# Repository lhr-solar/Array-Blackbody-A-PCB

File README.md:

# RTD and Irradiance Sensor Board

This repository contains the following files for the RTD/Irradiance Sensor HW:

- Schematic
- Layout
- Datasheets

Also a good resource is the
[Irradiance/RTD Board Parts List](https://docs.google.com/spreadsheets/d/1edYMT-QyYtll1uI2qYTIh2mhwAQPUqRFkjrvS2jViS4/edit?usp=sharing);
this is the source of truth for the schematic and layout and should be consulted
and updated by anyone doing revisions on the board. As good practice, make sure
your updates to the parts list, when finalized, gets a new named version in the
version history.

A couple other important sections for engineers who are improving this board are
below.

- Versioning
- Maintainers
- Errata and Changes
- Suggested Improvements
- Ordering Instructions
- Assembly Instructions

---

## Maintainers

The last maintainer of this project was Matthew Yu (Array Lead 2020) as of
12/13/2020. His email is matthewjkyu@gmail.com.

Also a useful point of contact is Professor Gary Hallock, who advised Matthew
and worked with the several former senior design teams and solar car class
groups who developed this board.

---

## Versioning, Errata, and Changes

This board has separate versions for the schematic, parts list, and layout. We
use [semantic versioning](https://semver.org/) to denote between versions.

We also follow the mutually inclusive versioning procedure agreed upon in this
[issue](https://github.com/lhr-solar/Electronics/issues/40).

### Versioning

The board schematic is currently on **Version 1.0.0**.

The board layout is currently on **Version 1.0.0**.

The parts list is currently on **Version 1.0.0**.

### Schematic

- **Rev 1.0.0**:
  - None as of 12/13/2020, but then the board hasn't been assembled and tested
    yet.

### Layout

- **Rev 1.0.0**:
  - None as of 12/13/2020, but then the board hasn't been assembled and tested
    yet.

### Parts List

- **Rev 1.0.0**:
  - Populated and ready for ordering (sans snubber caps and resistors).

---

## Suggested Improvements

This is a list of changes we can make to the board in future versions to improve
it in various ways. Some of these are functional, others are purely aesthetic.

1. Use a multiplexer to route RTDs to a single RTD-to-digital-converter chip.
   This would reduce our 8 chips into 1 and potentially cut down board size by
   more than 50%. This may also have advantages for digital signal integrity by
   drastically reducing trace length. Oh, and a large cost reduction.
2. Rename the project from RTDTemp to RTD_Irradiance_Board. Make sure you do
   this on a feature branch of the repo so you can revert to a previous version
   if you break things.

---

## Ordering Instructions

Ordering the board will vary from distributor to distributor; some will take the
KiCAD project directly, others require Gerber files. If they require gerber
files, some will require specific naming conventions for each layer.

If they take KiCAD projects directly, that should be what you prefer. Package
`RTDTemp.pro`, `RTDTemp.kicad_pcb`, and `RTDTemp.sch` together into a zip file (i.e.
`RTDTemp.zip`) and upload it. Double check the layers they detect to ensure that
everything looks correct. If they aren't interpreted correctly, use the Gerber
files instead.

The Gerber files are grouped together into the 'Gerber/' folder. The layers you
want are:

- Front/Top Copper,
- Back/Bottom Copper,
- Front/Top Mask,
- Back/Bottom Mask,
- Front/Top Silkscreen,
- Back/Bottom Silkscreen,
- Edge Cuts (i.e. board outline)

You may also want the Front/Top Fabrication layer if you're submitting to a
manufacturer that will place and solder your components for you, but that's not
strictly necessary.

The Gerber files I've generated should be named appropriately for most
manufacturers, however they may prefer slightly different conventions. Double
check their requirements, make any necessary adjustments to file names, then zip
up all of the gerber files and upload that.

Some examples of alternate conventions:

- Some want the board outline to have the extension '.gko'.
- Some want all layers to have the same base name (i.e. 'RTDTemp.gbl',
  'RTDTemp.gbs', etc.).
- Some want the drill files combined (in which case you'll need to regenerate
  the drill file with plated and nonplated holes combined).
- Some want the drill files to have the extension '.txt'.

If you need to regenerate the Gerber files for whatever reason, the defaults
saved to the PCB file should be sufficient. However, in case these are lost,
here are the important parts:

- Set Output Directory to "Gerber/"
- Uncheck "Plot sheet reference on all layers"
- Check "Exclude PCB edge layer from other layers"
- Check "Use Protel filename extensions"

-or the drill files:

- Set Output Directory to "Gerber/"
- Set Drill Units to "Inches"
- Set Zeros Format to "Decimal format"
- Set Drill Map File Format to "PostScript"
- Uncheck "Mirror y axis"

These settings should work, but double check with your manufacturer that these
settings are correct before you order.

---

## Assembly and Testing

The board should be assembled and tested in sections to ensure proper
functioning. Assembly should go through the following sections in order:

1. Power Regulation
2. LEDs
3. Nucleo Connections
4. RTD Sensors
5. Irradiance Sensors
6. CAN

### Step by Step Instructions

It's highly recommended to pull up the schematic and layout side by side while
assembling and testing the board. As a tip, you can click on the schematic
symbol, and if the layout window is open, it'll jump to that part on the layout.
Also hide everything except the Silkscreen or Fabrication layer (of the right
side of the PCB) to remove any clutter from the layout.

Also, if you find any discrepancies between these instructions and the board
layout, please file a PR or issue so it can be fixed!

1. Initial Board Checks

   Before installing anything, check for power shorts where there shouldn't be:
   - Between Car Power +12V and GNDPWR.
   - Between Device Power +9VA and GNDREF.
   - Between Car Power +12V and Device Power +9VA.
   - Between Car Power GNDPWR and Device Power GNDREF.
   - Between CAN Iso Vout and GndOut
   - Between CAN Iso Vin and GndIn
   - Between CAN Iso Vout and Vin
   - Between CAN Iso GndOut and GndIn

   Other important shorts to check for and eliminate:
   - Between CAN H and L
   - On each Nucleo board, between A4 and D4 (shorted by SB18)
   - On each Nucleo board, between A5 and D5 (shorted by SB16)

2. Assembling Power Regulation
   1. Solder the smallest components first: L1, C1, C2, C3, C4. These can be
      done in any order.
   2. Solder test points: TP2, TP3, TP4, TP5. These can be done in any order.
   3. Solder power regulator U2.
   4. Solder the connector J3.
   5. Test for the following shorts:
      - Between Car Power +12V and GNDPWR.
      - Between Device Power +9VA and GNDREF.
      - Between Car Power +12V and Device Power +9VA.
      - Between Car Power GNDPWR and Device Power GNDREF.
      - Between pins on U2.
   6. Connect +12V to the connector and verify that +9VA is at TP4.
   7. As a bonus, somehow make some noise at +12V and see how stable +9VA is.

3. LEDs
   1. Solder the smallest components first: R3 - R8 and LED1 - LED6. You get the
      drill by now.
   2. Check for shorts across each resistor-LED pair. As a tip, the LED
      reference number is always two less than the resistor reference number.
   3. Further testing on these will occur in the next step.

4. Nucleo Connections
   1. Solder the smallest components first: SW, J1, J2, R1, R2. You get the
      drill by now.
   2. Solder the headers for the Nucleo (U1) and make sure they are upright.
   3. Test for the following shorts:
      - Across SW1 (shorts only when pushed)
      - Between pins on U1 (as a bonus)
   4. Plug in the Nucleo and then test for shorts between D4 and A4 and between
      D5 and A5. If there are shorts here, you will need to remove SB18 or SB16,
      respectively, from the Nucleo board.

      **YOU MUST DO THIS FOR EVERY UNIQUE NUCLEO YOU PLUG INTO THE BOARD.**

   5. Load up the Nucleo with a test program to cycle LED pins and outputs a PWM
      signal with a non-trivial duty cycle and see if they light up/are correct
      on an O-scope. Unplug the Nucleo from USB, and connect 12V to the Car
      Power Connector J1 (But not both!). Make sure the Nucleo powers on again
      and the test program works as expected.
   6. Remove the Nucleo and all sources of power before further assembly.

5. RTD Sensors

   It's recommended to do one of these sensors at a time.

   1. Pick a sensor. We'll use the first sensor (sensor 0) as an example.
   2. Solder the smallest components first: RTD0_C1, RTD0_C2, RTD0_C3, RTD0_R1.
   3. Solder the chip RTD0_U1.
   4. Solder the connector RTD0_J1.
   5. Test for shorts across the pins on U1, and that we have a connection
      between pads 2 and 3 and the +3.3V pin of the Nucleo (after
      plugging it in, but not powering it).
   6. You can then load up a test program to communicate with the chip via SPI.
      If you have an Arduino Uno, you can try using this
      [test program](https://github.com/olewolf/arduino-max31865)
      written by `olewolf`. You can use the Nucleo headers to access the
      relevant pins of the chips - the pin mapping is described in the
      `Examples/Read_Temperature/Read_Temperature.ino`.
   7. If test software for the Nucleo has been written, you can potentially skip
      step 6 and use the Nucleo with the software flashed directly. Although
      going back to step 6 could be useful for debugging if you have issues
      here.

6. CAN Circuit

   1. Solder chip U3 **first** and test for shorts across adjacent pins.
   2. Solder the smallest components: C5 - C12, L2, L3, R10, R11.
   3. Solder bridge R9.
   4. Solder test points TP5 - TP12.
   5. Solder the chip U4.
   6. Solder the termination header JP1.
   7. Solder the CAN Connectors J4, J5.
   8. Test for the following shorts:
      - Between CAN_H and CAN_L.
      - Between CAN_Tx, CAN_Rx.
      - +5V and GNDREF (Power side).
      - 5V and GND (CAN side).
      - Across adjacent pins in U3, U4.
   9. Plug in the Nucleo, connect J4/J5 to a CAN bus, and run a CAN
      communication test to ensure that the installed CAN circuitry is
      functional.
   10. Remove any power, the Nucleo, and then CAN connections before further
       assembly.

7. Post checks

   Now that you've made it to the end (we hope) of assembly and preliminary
   testing, you should do a couple things before running full RTDTemp tests and
   running RTDTemp algorithms on it.

   1. First, check the board for obvious soldering defections like burnt traces
      or exposed component legs. Make sure those still work. For any solder
      bridges that shouldn't fix, you should fix them. Or get somebody who's
      better than you to fix them.
   2. Check to see if you have any remaining parts hiding in the pile of
      plastic packages you probably received. Any remaining parts should
      probably be a cause for concern (unless you knew you were going to blow
      something and had the foresight to get extra) and you should definitely
      see where they might have come from.

      The RTDTemp Parts list is **THE** definite source of truth, and tells you
      where each part is tied to which reference and thus their position on the
      layout. Check there first before running to the electrical lead to help
      you.
   3. It might be a good idea if you're bored to run any electrical/short tests
      that were described earlier in these instructions. There's always a small
      chance that some assembly you did later on broke/removed/damaged previous
      parts.

You now have a completed RTDTemp (I hope) and I wish you luck in your future
solar car endeavors!

This assembly guide was last modified *12/13/2020* by **Matthew Yu**.

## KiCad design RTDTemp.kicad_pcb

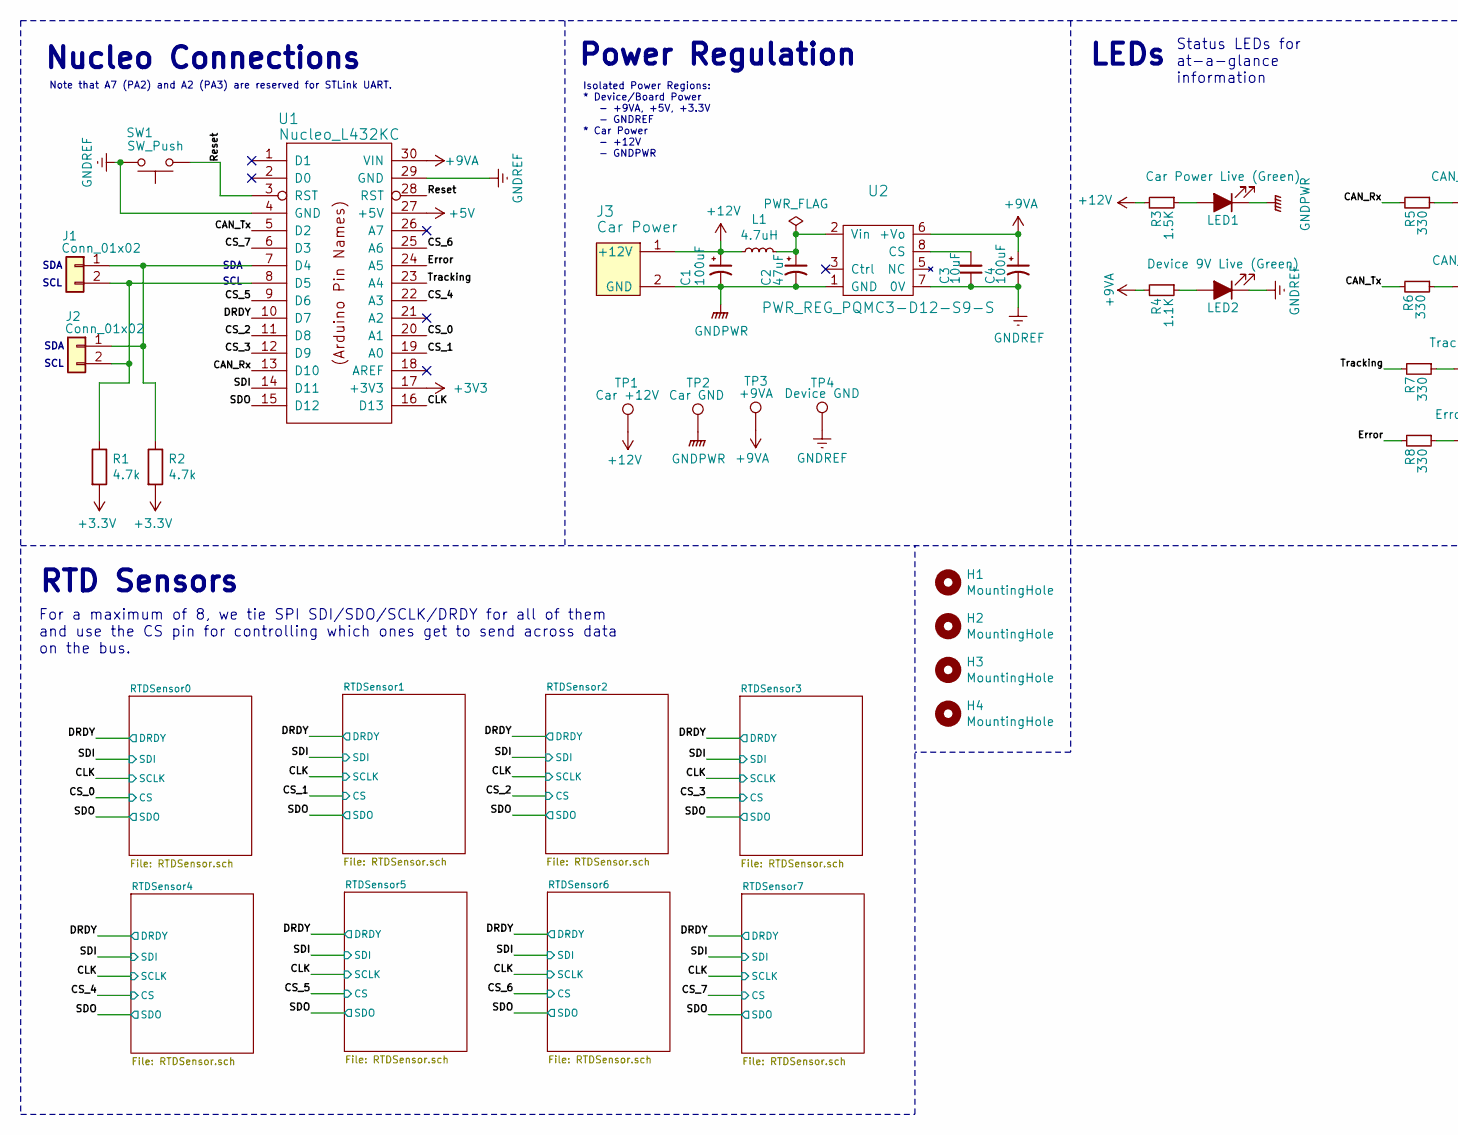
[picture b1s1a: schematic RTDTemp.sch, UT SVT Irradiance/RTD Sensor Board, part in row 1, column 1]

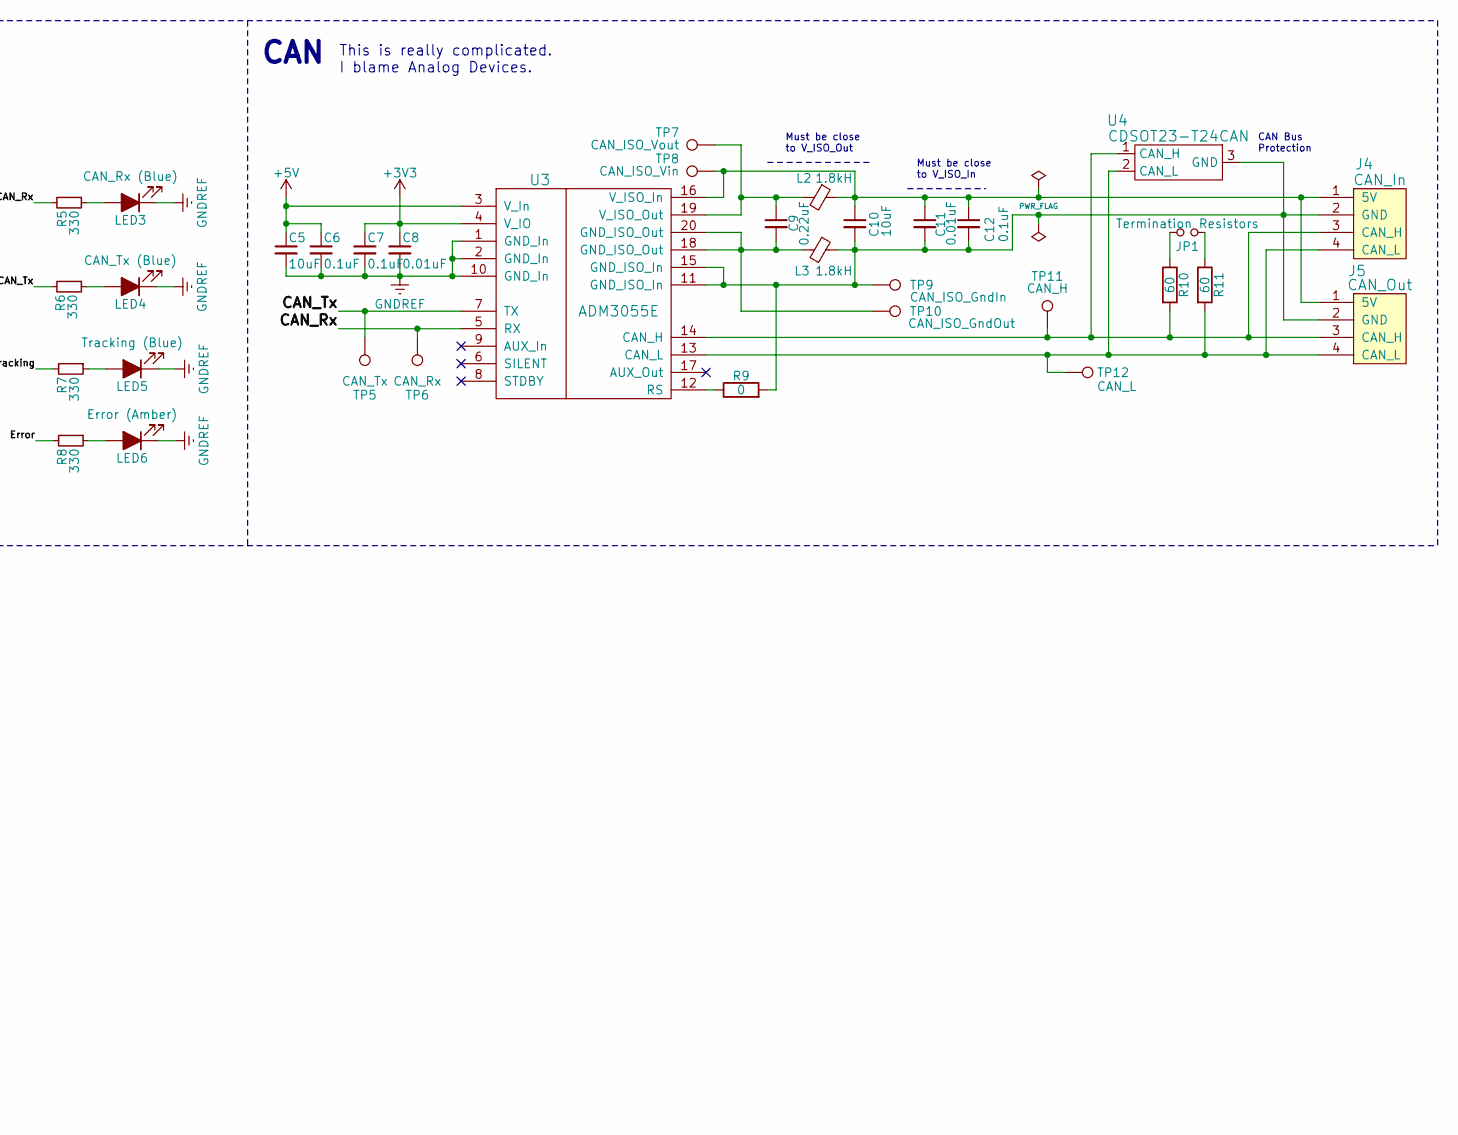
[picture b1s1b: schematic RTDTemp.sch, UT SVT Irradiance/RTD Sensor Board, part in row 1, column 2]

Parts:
C1, C4: 100uF; C_1210_3225Metric
C2: 47uF; C_1210_3225Metric
C3, C5, C10: 10uF; C_0805_2012Metric
C6, C7, C12: 0.1uF; C_0805_2012Metric
C8, C11: 0.01uF; C_0805_2012Metric
C9: 0.22uF; C_0805_2012Metric
H1, H2, H3, H4: MountingHole; MountingHole_3mm
J1, J2: Conn_01x02; Molex_Micro-Fit_3.0_43650-0215_1x02_P3.00mm_Vertical
J3: Car Power; Molex_Micro-Fit_3.0_43650-0215_1x02_P3.00mm_Vertical
J4: CAN_In; Molex_Micro-Fit_3.0_43650-0415_1x04_P3.00mm_Vertical
J5: CAN_Out; Molex_Micro-Fit_3.0_43650-0415_1x04_P3.00mm_Vertical
JP1: Termination Resistors; PinHeader_1x02_P2.54mm_Vertical
L1: 4.7uH; L_0805_2012Metric
L2, L3: 1.8kH; L_0805_2012Metric
LED1: Car Power Live (Green); LED_0805_2012Metric
LED2: Device 9V Live (Green); LED_0805_2012Metric
LED3: CAN_Rx (Blue); LED_0805_2012Metric
LED4: CAN_Tx (Blue); LED_0805_2012Metric
LED5: Tracking (Blue); LED_0805_2012Metric
LED6: Error (Amber); LED_0805_2012Metric
R1, R2: 4.7k; R_0805_2012Metric
R3: 1.5K; R_0805_2012Metric
R4: 1.1K; R_0805_2012Metric
R5, R6, R7, R8: 330; R_0805_2012Metric
R9: 0; R_0805_2012Metric
R10, R11: 60; R_0805_2012Metric
SW1: SW_Push; SW_PUSH_6mm
TP1: Car +12V; TestPoint_Keystone_5005-5009_Compact
TP2: Car GND; TestPoint_Keystone_5005-5009_Compact
TP3: +9VA; TestPoint_Keystone_5005-5009_Compact
TP4: Device GND; TestPoint_Keystone_5005-5009_Compact
TP5: CAN_Tx; TestPoint_Keystone_5005-5009_Compact
TP6: CAN_Rx; TestPoint_Keystone_5005-5009_Compact
TP7: CAN_ISO_Vout; TestPoint_Keystone_5005-5009_Compact
TP8: CAN_ISO_Vin; TestPoint_Keystone_5005-5009_Compact
TP9: CAN_ISO_GndIn; TestPoint_Keystone_5005-5009_Compact
TP10: CAN_ISO_GndOut; TestPoint_Keystone_5005-5009_Compact
TP11: CAN_H; TestPoint_Keystone_5005-5009_Compact
TP12: CAN_L; TestPoint_Keystone_5005-5009_Compact
U1: Nucleo_L432KC; MODULE_NUCLEO-L432KC
U2: PWR_REG_PQMC3-D12-S9-S; 490_PQMC3_D12_S12_S
U3: ADM3055E; ADM3055EBRIZ
U4: CDSOT23-T24CAN; SOT-23

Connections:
+5V: C5.1, C6.1, U1.27 (+5V), U3.3 (V_In)
+9VA: C4.1, R4.2, TP3.1, U1.30 (VIN), U2.6 (+Vo)
+12V: C1.1, J3.1 (+12V), L1.1, R3.2, TP1.1
/CAN_Rx: R5.2, TP6.1, U1.13 (D10), U3.5 (RX)
/CAN_Tx: R6.2, TP5.1, U1.5 (D2), U3.7 (TX)
/CLK: U1.16 (D13); also elsewhere on the board
/CS_0: U1.20 (A1); also elsewhere on the board
/CS_1: U1.19 (A0); also elsewhere on the board
/CS_2: U1.11 (D8); also elsewhere on the board
/CS_3: U1.12 (D9); also elsewhere on the board
/CS_4: U1.22 (A3); also elsewhere on the board
/CS_5: U1.9 (D6); also elsewhere on the board
/CS_6: U1.25 (A6); also elsewhere on the board
/CS_7: U1.6 (D3); also elsewhere on the board
/DRDY: U1.10 (D7); also elsewhere on the board
/Error: R8.2, U1.24 (A5)
/Reset: SW1.1, U1.3 (RST), U1.28 (RST)
/SDI: U1.14 (D11); also elsewhere on the board
/SDO: U1.15 (D12); also elsewhere on the board
/Tracking: R7.2, U1.23 (A4)
GNDPWR: C1.2, C2.2, J3.2 (GND), LED1.1 (K), TP2.1, U2.1 (GND)
GNDREF: C3.1, C4.2, C5.2, C6.2, C7.2, C8.2, LED2.1 (K), LED3.1 (K), LED4.1 (K), LED5.1 (K), LED6.1 (K), SW1.2, TP4.1, U1.4 (GND), U1.29 (GND), U2.7 (0V), U3.1 (GND_In), U3.2 (GND_In), U3.10 (GND_In); also elsewhere on the board
unnamed: C2.1, L1.2, U2.2 (Vin)
unnamed: C3.2, U2.8 (CS)
unnamed: C9.1, L2.2, TP7.1, U3.19 (V_ISO_Out)
unnamed: C9.2, L3.2, TP10.1, U3.18 (GND_ISO_Out), U3.20 (GND_ISO_Out)
unnamed: C10.1, C11.1, C12.1, J4.1 (5V), J5.1 (5V), L2.1, TP8.1, U3.16 (V_ISO_In)
unnamed: C10.2, C11.2, C12.2, J4.2 (GND), J5.2 (GND), L3.1, R9.2, TP9.1, U3.11 (GND_ISO_In), U3.15 (GND_ISO_In), U4.3 (GND)
unnamed: J1.1, J2.1, R2.1, U1.7 (D4)
unnamed: J1.2, J2.2, R1.1, U1.8 (D5)
unnamed: J4.3 (CAN_H), J5.3 (CAN_H), R10.2, TP11.1, U3.14 (CAN_H), U4.1 (CAN_H)
unnamed: J4.4 (CAN_L), J5.4 (CAN_L), R11.2, TP12.1, U3.13 (CAN_L), U4.2 (CAN_L)
unnamed: JP1.1, R11.1
unnamed: JP1.2, R10.1
unnamed: LED1.2 (A), R3.1
unnamed: LED2.2 (A), R4.1
unnamed: LED3.2 (A), R5.1
unnamed: LED4.2 (A), R6.1
unnamed: LED5.2 (A), R7.1
unnamed: LED6.2 (A), R8.1
unnamed: R9.1, U3.12 (RS)

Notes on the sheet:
RTD Sensors
For a maximum of 8, we tie SPI SDI/SDO/SCLK/DRDY for all of them and use the CS pin for controlling which ones get to send across data on the bus.
CAN Bus Protection
Must be close to V_ISO_In
Must be close to V_ISO_Out
This is really complicated. I blame Analog Devices.
CAN
Nucleo Connections
SDA
SCL
Note that A7 (PA2) and A2 (PA3) are reserved for STLink UART.
Power Regulation
Isolated Power Regions: * Device/Board Power - +9VA, +5V, +3.3V - GNDREF * Car Power - +12V - GNDPWR
LEDs
Status LEDs for at-a-glance information

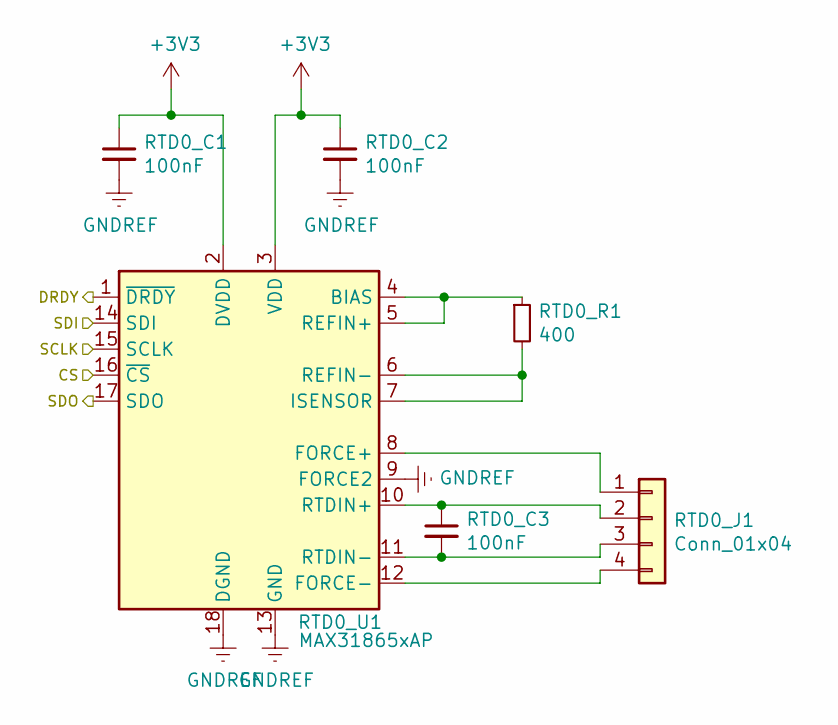
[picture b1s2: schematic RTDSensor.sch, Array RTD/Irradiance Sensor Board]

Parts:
RTD1_C1, RTD1_C2, RTD1_C3: 100nF; C_0805_2012Metric
RTD1_J1: Conn_01x04; Molex_Micro-Fit_3.0_43650-0415_1x04_P3.00mm_Vertical
RTD1_R1: 400; R_0805_2012Metric
RTD1_U1: MAX31865xAP; SSOP-20_5.3x7.2mm_P0.65mm

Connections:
/CLK: RTD1_U1.15 (SCLK); also elsewhere on the board
/CS_1: RTD1_U1.16 (~CS); also elsewhere on the board
/DRDY: RTD1_U1.1 (~DRDY); also elsewhere on the board
/SDI: RTD1_U1.14 (SDI); also elsewhere on the board
/SDO: RTD1_U1.17 (SDO); also elsewhere on the board
GNDREF: RTD1_C1.2, RTD1_C2.2, RTD1_U1.9 (FORCE2), RTD1_U1.13 (GND), RTD1_U1.18 (DGND), RTD1_U1.19 (GND); also elsewhere on the board
unnamed: RTD1_C3.1, RTD1_J1.2, RTD1_U1.10 (RTDIN+)
unnamed: RTD1_C3.2, RTD1_J1.3, RTD1_U1.11 (RTDIN-)
unnamed: RTD1_J1.1, RTD1_U1.8 (FORCE+)
unnamed: RTD1_J1.4, RTD1_U1.12 (FORCE-)
unnamed: RTD1_R1.1, RTD1_U1.4 (BIAS), RTD1_U1.5 (REFIN+)
unnamed: RTD1_R1.2, RTD1_U1.6 (REFIN-), RTD1_U1.7 (ISENSOR)

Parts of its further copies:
RTD0_C1, RTD0_C2, RTD0_C3, RTD2_C1, RTD2_C2, RTD2_C3, RTD3_C1, RTD3_C2, RTD3_C3, RTD4_C1, RTD4_C2, RTD4_C3, RTD5_C1, RTD5_C2, RTD5_C3, RTD6_C1, RTD6_C2, RTD6_C3, RTD7_C1, RTD7_C2, RTD7_C3: 100nF; C_0805_2012Metric
RTD0_J1, RTD2_J1, RTD3_J1, RTD4_J1, RTD5_J1, RTD6_J1, RTD7_J1: Conn_01x04; Molex_Micro-Fit_3.0_43650-0415_1x04_P3.00mm_Vertical
RTD0_R1, RTD2_R1, RTD3_R1, RTD4_R1, RTD5_R1, RTD6_R1, RTD7_R1: 400; R_0805_2012Metric
RTD0_U1, RTD2_U1, RTD3_U1, RTD4_U1, RTD5_U1, RTD6_U1, RTD7_U1: MAX31865xAP; SSOP-20_5.3x7.2mm_P0.65mm

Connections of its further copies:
/CLK: RTD0_U1.15 (SCLK), RTD2_U1.15 (SCLK), RTD3_U1.15 (SCLK), RTD4_U1.15 (SCLK), RTD5_U1.15 (SCLK), RTD6_U1.15 (SCLK), RTD7_U1.15 (SCLK); also elsewhere on the board
/CS_0: RTD0_U1.16 (~CS); also elsewhere on the board
/CS_2: RTD2_U1.16 (~CS); also elsewhere on the board
/CS_3: RTD3_U1.16 (~CS); also elsewhere on the board
/CS_4: RTD4_U1.16 (~CS); also elsewhere on the board
/CS_5: RTD5_U1.16 (~CS); also elsewhere on the board
/CS_6: RTD6_U1.16 (~CS); also elsewhere on the board
/CS_7: RTD7_U1.16 (~CS); also elsewhere on the board
/DRDY: RTD0_U1.1 (~DRDY), RTD2_U1.1 (~DRDY), RTD3_U1.1 (~DRDY), RTD4_U1.1 (~DRDY), RTD5_U1.1 (~DRDY), RTD6_U1.1 (~DRDY), RTD7_U1.1 (~DRDY); also elsewhere on the board
/SDI: RTD0_U1.14 (SDI), RTD2_U1.14 (SDI), RTD3_U1.14 (SDI), RTD4_U1.14 (SDI), RTD5_U1.14 (SDI), RTD6_U1.14 (SDI), RTD7_U1.14 (SDI); also elsewhere on the board
/SDO: RTD0_U1.17 (SDO), RTD2_U1.17 (SDO), RTD3_U1.17 (SDO), RTD4_U1.17 (SDO), RTD5_U1.17 (SDO), RTD6_U1.17 (SDO), RTD7_U1.17 (SDO); also elsewhere on the board
GNDREF: RTD0_C1.2, RTD0_C2.2, RTD0_U1.9 (FORCE2), RTD0_U1.13 (GND), RTD0_U1.18 (DGND), RTD0_U1.19 (GND), RTD2_C1.2, RTD2_C2.2, RTD2_U1.9 (FORCE2), RTD2_U1.13 (GND), RTD2_U1.18 (DGND), RTD2_U1.19 (GND), RTD3_C1.2, RTD3_C2.2, RTD3_U1.9 (FORCE2), RTD3_U1.13 (GND), RTD3_U1.18 (DGND), RTD3_U1.19 (GND), RTD4_C1.2, RTD4_C2.2, RTD4_U1.9 (FORCE2), RTD4_U1.13 (GND), RTD4_U1.18 (DGND), RTD4_U1.19 (GND), RTD5_C1.2, RTD5_C2.2, RTD5_U1.9 (FORCE2), RTD5_U1.13 (GND), RTD5_U1.18 (DGND), RTD5_U1.19 (GND), RTD6_C1.2, RTD6_C2.2, RTD6_U1.9 (FORCE2), RTD6_U1.13 (GND), RTD6_U1.18 (DGND), RTD6_U1.19 (GND), RTD7_C1.2, RTD7_C2.2, RTD7_U1.9 (FORCE2), RTD7_U1.13 (GND), RTD7_U1.18 (DGND), RTD7_U1.19 (GND); also elsewhere on the board
unnamed: RTD0_C3.1, RTD0_J1.2, RTD0_U1.10 (RTDIN+)
unnamed: RTD0_C3.2, RTD0_J1.3, RTD0_U1.11 (RTDIN-)
unnamed: RTD0_J1.1, RTD0_U1.8 (FORCE+)
unnamed: RTD0_J1.4, RTD0_U1.12 (FORCE-)
unnamed: RTD0_R1.1, RTD0_U1.4 (BIAS), RTD0_U1.5 (REFIN+)
unnamed: RTD0_R1.2, RTD0_U1.6 (REFIN-), RTD0_U1.7 (ISENSOR)
unnamed: RTD2_C3.1, RTD2_J1.2, RTD2_U1.10 (RTDIN+)
unnamed: RTD2_C3.2, RTD2_J1.3, RTD2_U1.11 (RTDIN-)
unnamed: RTD2_J1.1, RTD2_U1.8 (FORCE+)
unnamed: RTD2_J1.4, RTD2_U1.12 (FORCE-)
unnamed: RTD2_R1.1, RTD2_U1.4 (BIAS), RTD2_U1.5 (REFIN+)
unnamed: RTD2_R1.2, RTD2_U1.6 (REFIN-), RTD2_U1.7 (ISENSOR)
unnamed: RTD3_C3.1, RTD3_J1.2, RTD3_U1.10 (RTDIN+)
unnamed: RTD3_C3.2, RTD3_J1.3, RTD3_U1.11 (RTDIN-)
unnamed: RTD3_J1.1, RTD3_U1.8 (FORCE+)
unnamed: RTD3_J1.4, RTD3_U1.12 (FORCE-)
unnamed: RTD3_R1.1, RTD3_U1.4 (BIAS), RTD3_U1.5 (REFIN+)
unnamed: RTD3_R1.2, RTD3_U1.6 (REFIN-), RTD3_U1.7 (ISENSOR)
unnamed: RTD4_C3.1, RTD4_J1.2, RTD4_U1.10 (RTDIN+)
unnamed: RTD4_C3.2, RTD4_J1.3, RTD4_U1.11 (RTDIN-)
unnamed: RTD4_J1.1, RTD4_U1.8 (FORCE+)
unnamed: RTD4_J1.4, RTD4_U1.12 (FORCE-)
unnamed: RTD4_R1.1, RTD4_U1.4 (BIAS), RTD4_U1.5 (REFIN+)
unnamed: RTD4_R1.2, RTD4_U1.6 (REFIN-), RTD4_U1.7 (ISENSOR)
unnamed: RTD5_C3.1, RTD5_J1.2, RTD5_U1.10 (RTDIN+)
unnamed: RTD5_C3.2, RTD5_J1.3, RTD5_U1.11 (RTDIN-)
unnamed: RTD5_J1.1, RTD5_U1.8 (FORCE+)
unnamed: RTD5_J1.4, RTD5_U1.12 (FORCE-)
unnamed: RTD5_R1.1, RTD5_U1.4 (BIAS), RTD5_U1.5 (REFIN+)
unnamed: RTD5_R1.2, RTD5_U1.6 (REFIN-), RTD5_U1.7 (ISENSOR)
unnamed: RTD6_C3.1, RTD6_J1.2, RTD6_U1.10 (RTDIN+)
unnamed: RTD6_C3.2, RTD6_J1.3, RTD6_U1.11 (RTDIN-)
unnamed: RTD6_J1.1, RTD6_U1.8 (FORCE+)
unnamed: RTD6_J1.4, RTD6_U1.12 (FORCE-)
unnamed: RTD6_R1.1, RTD6_U1.4 (BIAS), RTD6_U1.5 (REFIN+)
unnamed: RTD6_R1.2, RTD6_U1.6 (REFIN-), RTD6_U1.7 (ISENSOR)
unnamed: RTD7_C3.1, RTD7_J1.2, RTD7_U1.10 (RTDIN+)
unnamed: RTD7_C3.2, RTD7_J1.3, RTD7_U1.11 (RTDIN-)
unnamed: RTD7_J1.1, RTD7_U1.8 (FORCE+)
unnamed: RTD7_J1.4, RTD7_U1.12 (FORCE-)
unnamed: RTD7_R1.1, RTD7_U1.4 (BIAS), RTD7_U1.5 (REFIN+)
unnamed: RTD7_R1.2, RTD7_U1.6 (REFIN-), RTD7_U1.7 (ISENSOR)

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
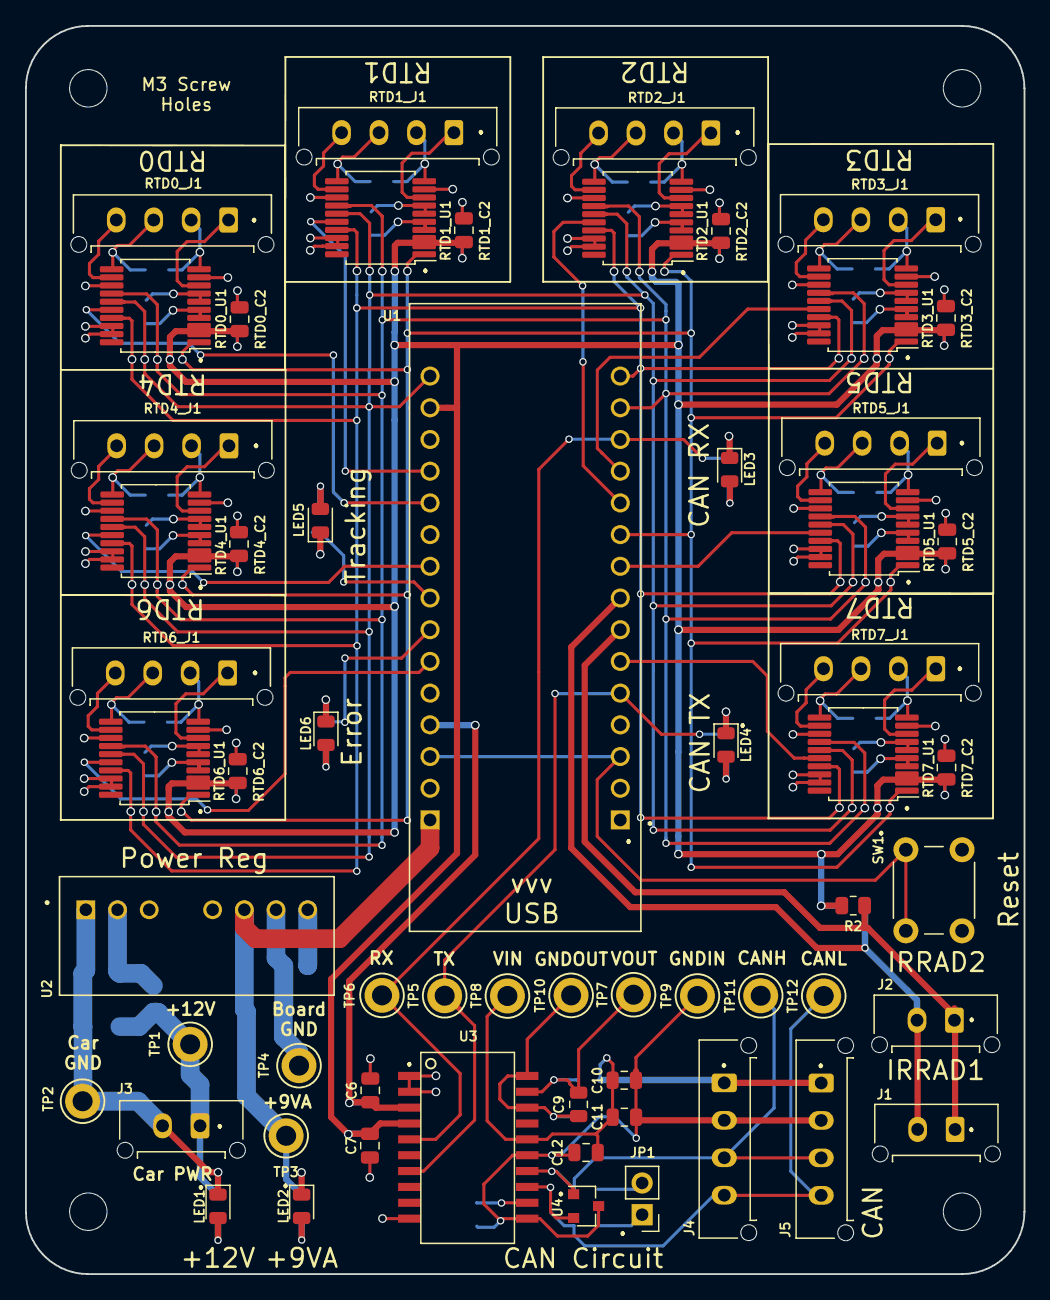
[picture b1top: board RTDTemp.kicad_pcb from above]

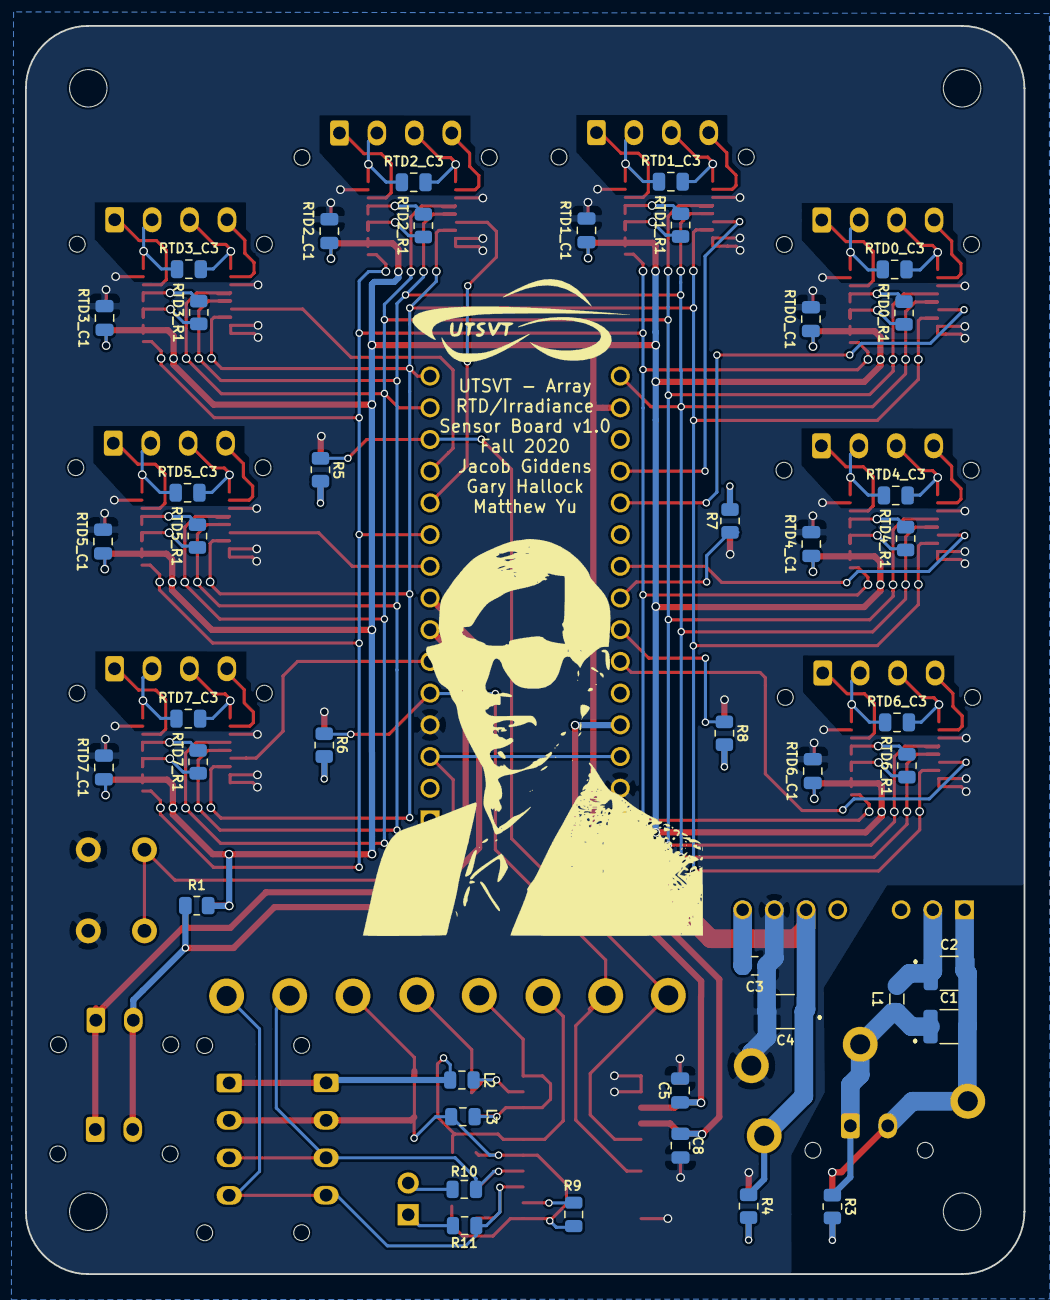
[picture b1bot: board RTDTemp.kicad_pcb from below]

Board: 2 copper layers, 80.0 x 100.0 mm, 107 parts (43 on the bottom side), 90 nets.

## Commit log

2020-08-02 Adapt RTD to the new repository.
2020-10-03 Adds QuAC
2020-10-10 Add the STEP model
2020-10-28 replacedOpAmpswithMaximChip
2020-10-28 Started RTD board layout update
2020-11-01 reset references for rtd specific components, preliminary layout of half of the RTD subcircuits
2020-11-07 Updated footprints and layout
2020-11-07 Arragned Board
    Arragned Board, room for optimization
2020-11-14 Finished Optimization, Edge cuts, and Placed Drill Holes
    Optimized the space as best as I could. Some more space could possibly be saved, or maybe some connections could be made better.
    Made the Edge Cuts for the boards. Dimensions right now are 70mm*90mm
    Placed Mounting Holes 5mm*5mm away from the corners of the board.
2020-11-16 cleanup of edge silkscreen and slight component reposition
2020-12-12 PR ready RTD/Irradiance Sensor Board. Added extra mounts for irradiance I2C and updated power reg to match MPPT. Also cleaner layout.
2020-12-12 Addressed review.
2020-12-14 Updated README with assembly and testing instructions.
2021-01-14 Added zip and step files
2021-03-07 Refill layers and rebuild gerbers.
2022-08-26 savestate
